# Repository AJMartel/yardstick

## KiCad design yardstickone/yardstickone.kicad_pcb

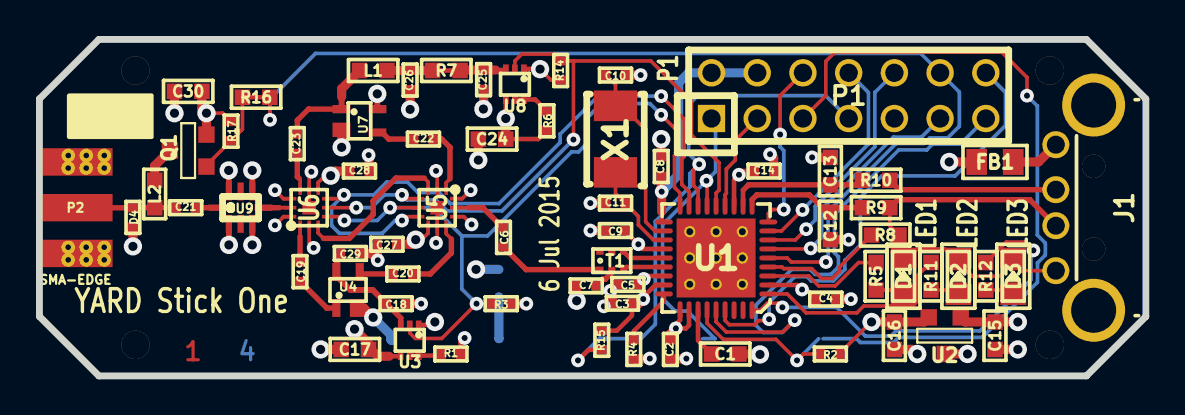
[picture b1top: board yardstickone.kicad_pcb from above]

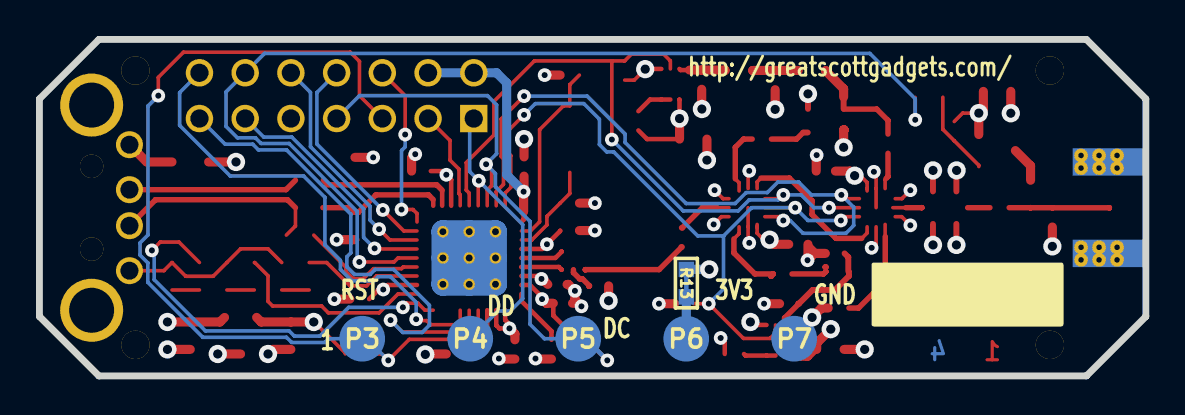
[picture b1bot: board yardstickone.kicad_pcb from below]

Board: 4 copper layers, 61.5 x 18.7 mm, 78 parts (6 on the bottom side), 58 nets.

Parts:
C1, C15, C17, C24, C30: 1uF; GSG-0603
C2, C4, C14, C27, C28: 100nF; GSG-0402
C3, C6, C7, C19, C20, C21, C22, C23, C29: 220pF; GSG-0402
C5, C8, C26: 10nF; GSG-0402
C9: 2p2; GSG-0402
C10, C11: 30pF; GSG-0402
C12, C13: 47pF; GSG-0603
C16: 4u7; GSG-0603
C18, C25: 22nF; GSG-0402
D1: LED1; GSG-0603D
D2: LED2; GSG-0603D
D3: LED3; GSG-0603D
D4: TVS_DIODE; GSG-0402
FB1: FILTER; GSG-0805
HOLE-62MIL, HOLE-62MIL#2, HOLE-62MIL#3, HOLE-62MIL#4: VAL**; GSG-HOLE-62MIL
J1: USB-DEVICE; GSG-USB-A-1001-010-01001-SHIELD
L1, L2: 1uH; GSG-0603
P1: CONN_02X07; GSG-HEADER-2x7
P2: SMA-EDGE; GSG-SMA-EDGE
P3: RESET_N; GSG-TESTPOINT-100MIL
P4: DD; GSG-TESTPOINT-100MIL
P5: DC; GSG-TESTPOINT-100MIL
P6: 3V3; GSG-TESTPOINT-100MIL
P7: GND; GSG-TESTPOINT-100MIL
Q1: MOSFET_P; SOT23-3GDS
R1, R2, R6, R15, R17: 4k7; GSG-0402
R3, R14: 1k; GSG-0402
R4: 56k; GSG-0402
R5, R12: 330; GSG-0603
R7, R13, R16: 0; GSG-0603-SHORT-10MIL
R8, R11: 1k5; GSG-0603
R9, R10: 33; GSG-0603
T1: BALUN; GSG-B0310J50100AHF
U1: CC1111; GSG-QFN36
U2: AP7313; GSG-SOT23-3
U3, U8: DMC2400; GSG-SOT563
U4: RX_AMP; GSG-SOT343
U5, U6: SKY13385; GSG-SKY13385
U7: TX_AMP; GSG-SOT343
U9: LPF; 0915LP15B026
X1: CRYSTAL; GSG-XTAL-TXC-7A

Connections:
3V3: C2.1, C3.2, C4.2, C5.2, C8.2, C9.2, C14.2, C16.1, C27.2, C28.2, C30.1, P1.2, P1.4, Q1.S, R2.2, R13.1, R15.1, R17.2, U1.2, U1.12, U1.19, U1.22, U1.25, U1.26, U1.28, U1.29, U2.2, U5.7, U6.7
/AMP_BYPASS_EN: U1.17, U5.6, U6.6
/ANT_BIAS_EN_N: Q1.G, R16.1, R17.1
/DC: P1.7, P5.1, R15.2, U1.16
/DD: P1.1, P4.1, U1.15
/P0_0: P1.12, R16.2, U1.5
/P0_1: P1.11, U1.6
/P0_2: P1.10, U1.7
/P0_3: P1.8, U1.8
/P0_4: P1.6, U1.9
/P0_5: P1.3, U1.13
/P1_1: R5.2, U1.3
/P1_2: R11.2, U1.1
/P1_3: R12.2, U1.36
/P1_6: P1.14, U1.33
/P1_7: P1.13, U1.32
/RESET_N: P1.5, P3.1, R2.1, U1.31
/RX_AMP_EN: R3.1, U1.18, U3.2, U5.5, U6.4
/TX_AMP_EN: R14.1, U1.14, U5.4, U6.5, U8.2
/VBUS: C15.1, C17.1, C24.1, FB1.1, R1.1, R6.1, U2.1, U3.4, U8.4
GND: C1.1, C2.2, C3.1, C4.1, C5.1, C7.2, C8.1, C9.1, C10.2, C11.2, C12.1, C13.1, C14.1, C15.2, C16.2, C17.2, C18.2, C24.2, C25.2, C26.2, C27.1, C28.1, C29.2, C30.2, D1.2, D2.2, D3.2, D4.1, J1.4, P1.9, P2.2, P7.1, R3.2, R4.2, R14.2, U1.0, U2.3, U3.1, U4.2, U5.0, U5.2, U5.8, U5.10, U5.12, U6.0, U6.2, U6.8, U6.10, U6.12, U7.2, U7.4, U8.1, U9.1, U9.3, U9.5, U9.7
unnamed: C1.2, U1.30
unnamed: C6.1, T1.1
unnamed: C6.2, U5.11
unnamed: C7.1, T1.2
unnamed: C10.1, U1.20, X1.1
unnamed: C11.1, U1.21, X1.2
unnamed: C12.2, R9.2, U1.10
unnamed: C13.2, R10.2, U1.11
unnamed: C18.1, C29.1, U3.3, U4.4
unnamed: C19.1, U4.1
unnamed: C19.2, U6.1
unnamed: C20.1, U5.9
unnamed: C20.2, U4.3
unnamed: C21.1, U9.8
unnamed: C21.2, D4.2, L2.2, P2.1
unnamed: C22.1, U5.1
unnamed: C22.2, U7.3
unnamed: C23.1, L1.1, U7.1
unnamed: C23.2, U6.9
unnamed: C25.1, R7.1, U8.3
unnamed: C26.1, L1.2, R7.2
unnamed: D1.1, R5.1
unnamed: D2.1, R11.1
unnamed: D3.1, R12.1
unnamed: FB1.2, J1.1
unnamed: J1.2, R10.1
unnamed: J1.3, R8.1, R9.1
unnamed: L2.1, Q1.D
unnamed: P6.1, R13.2
unnamed: R1.2, U3.5, U3.6
unnamed: R4.1, U1.27
unnamed: R6.2, U8.5, U8.6
unnamed: R8.2, U1.4
unnamed: T1.3, U1.24
unnamed: T1.4, U1.23
unnamed: U5.3, U6.3
unnamed: U6.11, U9.4

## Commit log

2016-11-20 Add some 3D shapes
2016-11-20 WIP update pcb file
2016-11-21 Add SMA connector
